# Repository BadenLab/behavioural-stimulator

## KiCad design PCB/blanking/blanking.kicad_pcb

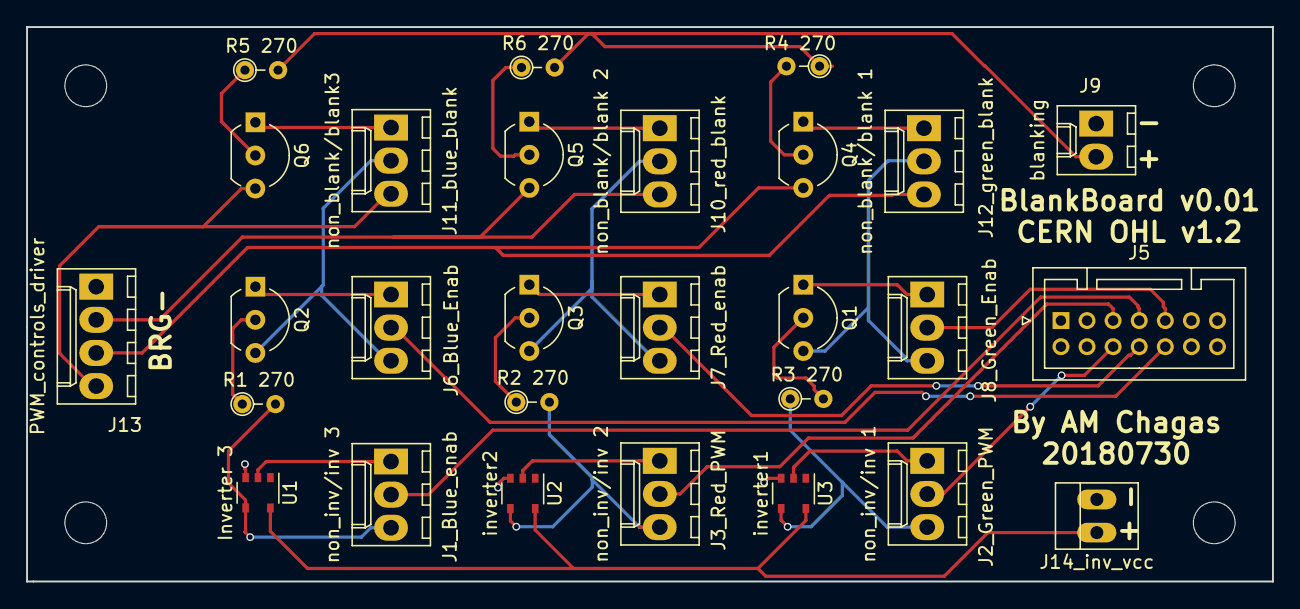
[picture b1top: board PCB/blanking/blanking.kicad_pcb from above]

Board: 2 copper layers, 95.5 x 42.5 mm, 28 parts (0 on the bottom side), 33 nets.

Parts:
J1_Blue_enab: non_inv/inv 3; Molex_KK-6410-03_03x2.54mm_Straight
J2_Green_PWM: non_inv/inv 1; Molex_KK-6410-03_03x2.54mm_Straight
J3_Red_PWM: non_inv/inv 2; Molex_KK-6410-03_03x2.54mm_Straight
J5: to_LCr_J29; JST_PUD_B14B-PUDSS_2x07x2.00mm_Straight
J6_Blue_Enab: Conn_01x03_Male blue; Molex_KK-6410-03_03x2.54mm_Straight
J7_Red_enab, J8_Green_Enab: Conn_01x03_Male; Molex_KK-6410-03_03x2.54mm_Straight
J9: blanking; Molex_KK-6410-02_02x2.54mm_Straight
J10_red_blank: non_blank/blank 2; Molex_KK-6410-03_03x2.54mm_Straight
J11_blue_blank: non_blank/blank3; Molex_KK-6410-03_03x2.54mm_Straight
J12_green_blank: non_blank/blank 1; Molex_KK-6410-03_03x2.54mm_Straight
J13: PWM_controls_driver; Molex_KK-6410-04_04x2.54mm_Straight
J14_inv_vcc: inv_vcc; PINHEAD1-2
Q1, Q2, Q3, Q4, Q5, Q6: Q_PNP_EBC; TO-92_Inline_Wide
R1 270, R2 270, R3 270, R4 270, R5 270, R6 270: R; R_Axial_DIN0204_L3.6mm_D1.6mm_P2.54mm_Vertical
U1: Inverter 3; TSOP-5_1.65x3.05mm_Pitch0.95mm
U2: inverter2; TSOP-5_1.65x3.05mm_Pitch0.95mm
U3: inverter1; TSOP-5_1.65x3.05mm_Pitch0.95mm

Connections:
GND: J5.12, J5.13, J5.14, J9.1, J13.1, J14_inv_vcc.2, U1.3, U2.3, U3.3
unnamed: J1_Blue_enab.1, U1.2
unnamed: J1_Blue_enab.2, J5.7
unnamed: J1_Blue_enab.3, R1 270.2, U1.4
unnamed: J2_Green_PWM.1, U3.2
unnamed: J2_Green_PWM.2, J5.6
unnamed: J2_Green_PWM.3, R3 270.1, U3.4
unnamed: J3_Red_PWM.1, U2.2
unnamed: J3_Red_PWM.2, J5.5
unnamed: J3_Red_PWM.3, R2 270.2, U2.4
unnamed: J5.8, J7_Red_enab.2
unnamed: J5.9, J8_Green_Enab.2
unnamed: J5.10, J6_Blue_Enab.2
unnamed: J6_Blue_Enab.1, Q2.1
unnamed: J7_Red_enab.1, Q3.1
unnamed: J8_Green_Enab.1, Q1.1
unnamed: J9.2, R4 270.1, R5 270.2, R6 270.2
unnamed: J10_red_blank.1, Q5.1
unnamed: J7_Red_enab.3, J10_red_blank.2, Q3.3
unnamed: J10_red_blank.3, J13.2, Q5.3
unnamed: J11_blue_blank.1, Q6.1
unnamed: J6_Blue_Enab.3, J11_blue_blank.2, Q2.3
unnamed: J11_blue_blank.3, J13.4, Q6.3
unnamed: J12_green_blank.1, Q4.1
unnamed: J8_Green_Enab.3, J12_green_blank.2, Q1.3
unnamed: J12_green_blank.3, J13.3, Q4.3
unnamed: J14_inv_vcc.1, U1.5, U2.5, U3.5
unnamed: Q1.2, R3 270.2
unnamed: Q2.2, R1 270.1
unnamed: Q3.2, R2 270.1
unnamed: Q4.2, R4 270.2
unnamed: Q5.2, R6 270.1
unnamed: Q6.2, R5 270.1

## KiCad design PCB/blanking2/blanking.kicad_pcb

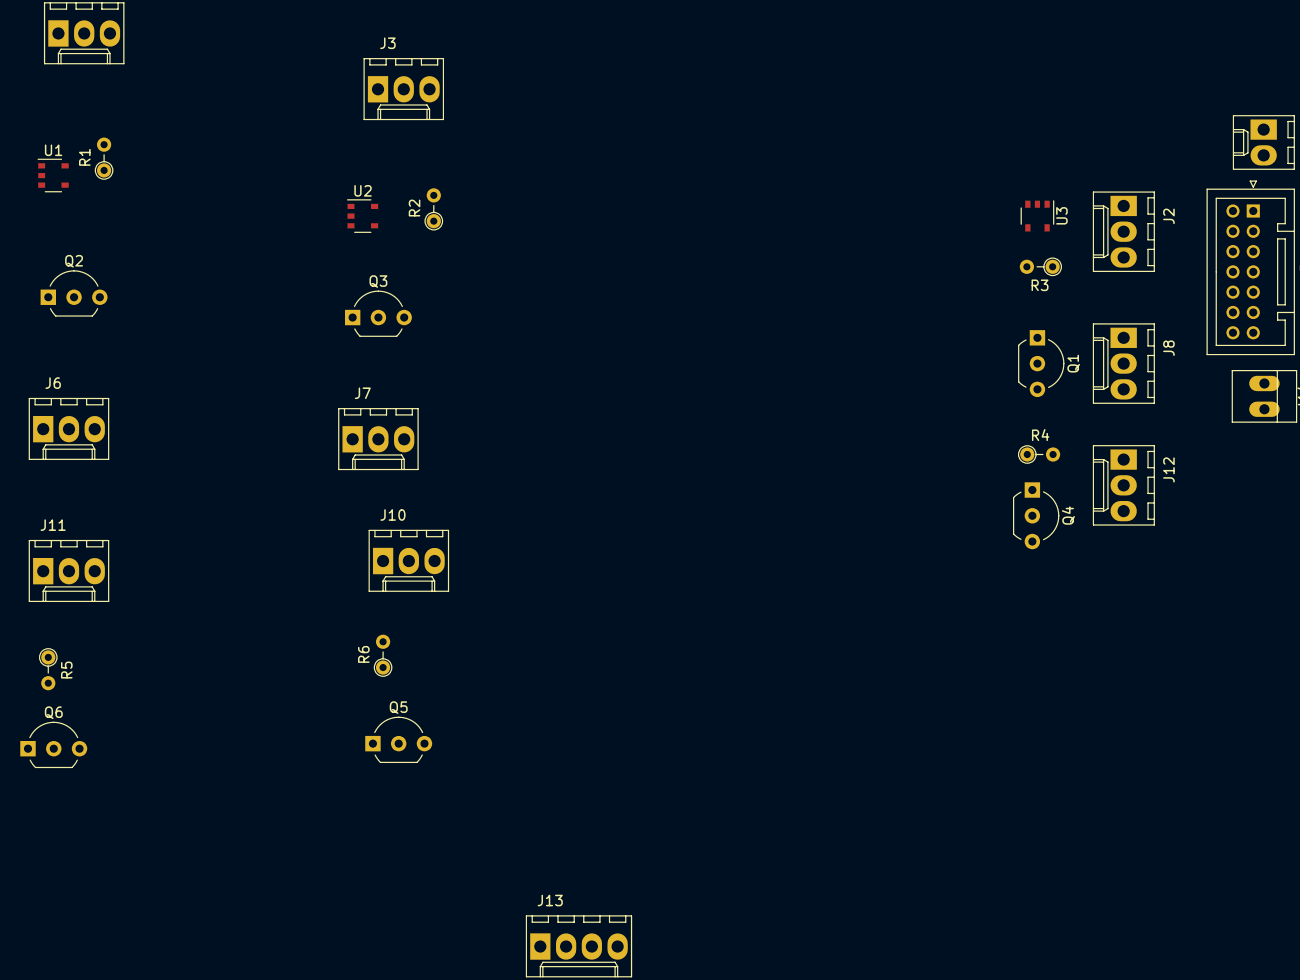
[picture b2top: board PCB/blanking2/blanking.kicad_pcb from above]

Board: 2 copper layers, 28 parts (0 on the bottom side), 33 nets, no tracks yet.

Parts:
J1, J2, J6, J7, J8, J10, J11, J12: Conn_01x03_Male; Molex_KK-6410-03_03x2.54mm_Straight
J3: invert_select; Molex_KK-6410-03_03x2.54mm_Straight
J5: to_LCr_J29; JST_PUD_B14B-PUDSS_2x07x2.00mm_Straight
J9: blanking; Molex_KK-6410-02_02x2.54mm_Straight
J13: PWM_controls_driver; Molex_KK-6410-04_04x2.54mm_Straight
J14: Conn_01x02; PINHEAD1-2
Q1, Q2, Q3, Q4, Q5, Q6: Q_PNP_EBC; TO-92_Inline_Wide
R1, R2, R3, R4, R5, R6: R; R_Axial_DIN0204_L3.6mm_D1.6mm_P2.54mm_Vertical
U1, U2, U3: 74AHC1G14; TSOP-5_1.65x3.05mm_Pitch0.95mm

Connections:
GND: J5.12, J5.13, J5.14, J9.1, J13.1, J14.2, U1.3, U2.3, U3.3
unnamed: J1.1, U1.2
unnamed: J1.2, J5.7
unnamed: J1.3, R1.2, U1.4
unnamed: J2.1, U3.2
unnamed: J2.2, J5.6
unnamed: J2.3, R3.1, U3.4
unnamed: J3.1, U2.2
unnamed: J3.2, J5.5
unnamed: J3.3, R2.2, U2.4
unnamed: J5.8, J7.2
unnamed: J5.9, J8.2
unnamed: J5.10, J6.2
unnamed: J6.1, Q2.1
unnamed: J7.1, Q3.1
unnamed: J8.1, Q1.1
unnamed: J9.2, R4.1, R5.2, R6.2
unnamed: J10.1, Q5.1
unnamed: J7.3, J10.2, Q3.3
unnamed: J10.3, J13.2, Q5.3
unnamed: J11.1, Q6.1
unnamed: J6.3, J11.2, Q2.3
unnamed: J11.3, J13.4, Q6.3
unnamed: J12.1, Q4.1
unnamed: J8.3, J12.2, Q1.3
unnamed: J12.3, J13.3, Q4.3
unnamed: J14.1, U1.5, U2.5, U3.5
unnamed: Q1.2, R3.2
unnamed: Q2.2, R1.1
unnamed: Q3.2, R2.1
unnamed: Q4.2, R4.2
unnamed: Q5.2, R6.1
unnamed: Q6.2, R5.1

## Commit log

2018-05-14 files to start
2018-05-14 initial bom.
2018-05-14 update to bom
2018-05-16 update bom, datasheets
2018-05-18 led specsheets, update bom, add fish cone spectra image
2018-05-18 update bom
2018-05-22 some updates to scad files
2018-05-22 adjust dichroic holder
    dichroic mirror now sits higher in the holder and fixing poles had their distance adjusted
2018-06-26 some changes to dichroich frame code
2018-06-26 remove temp file
2018-06-26 update with schematics and datasheets
2018-06-26 3d parts update
2018-07-04 update 3d files, correct small bug on dichroic holder
2018-07-04 add information about dichroics
2018-07-18 update some 3D printed parts
2018-07-18 Start PCB design
2018-07-20 created UVLED PCB updated main circuit
2018-07-27 update uv board
2018-07-30 update pcbs for production
2018-08-17 update to PCBs

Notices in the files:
PCB/blanking/blanking.kicad_pcb:
CERN OHL v1.2
